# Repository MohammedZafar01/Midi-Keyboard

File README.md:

This innovative project is a compact, custom instrument driven by an ESP32-S3 microcontroller that features capacitive touch keys instead of traditional mechanical keyboard switches. It incorporates two potentiometers and one rotary encoder for real-time parameter tweaking, alongside three toggle switches to seamlessly shift octaves or change musical play modes. Visual feedback is provided dynamically through three integrated LEDs. Because the design utilizes every single available hardware pin on the microcontroller, it relies entirely on its existing micro-USB port to transmit data rather than requiring extra audio outputs. By leveraging native USB MIDI capabilities, the device communicates directly with a computer or mobile phone to send instant, lightweight musical commands that trigger high-quality audio synthesis inside software like GarageBand or Ableton.

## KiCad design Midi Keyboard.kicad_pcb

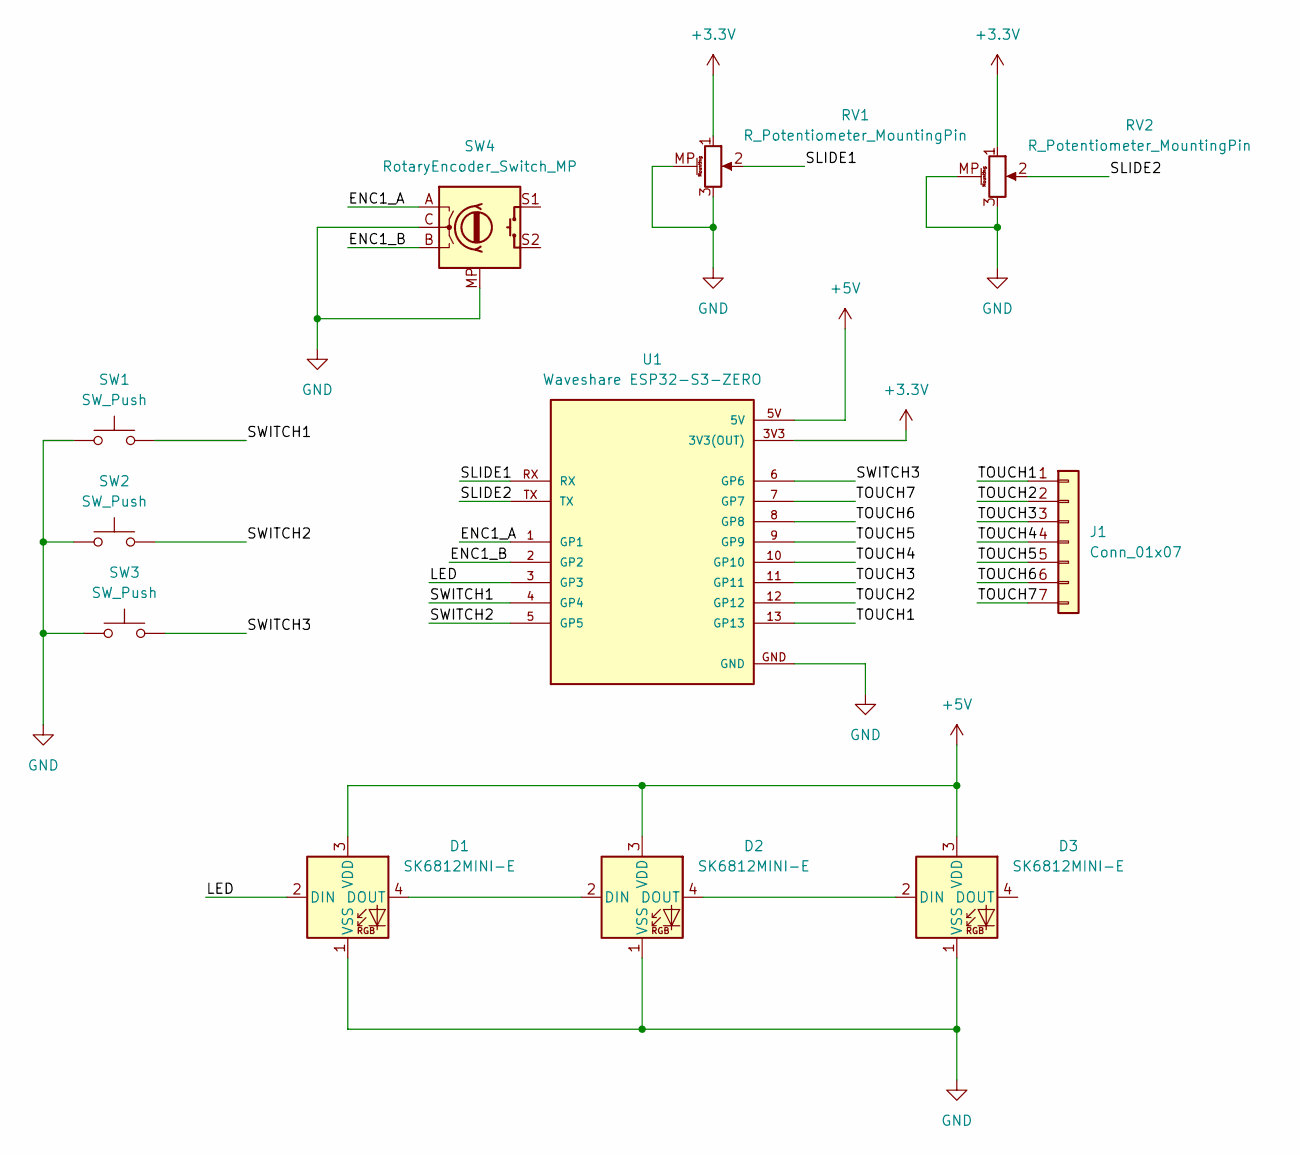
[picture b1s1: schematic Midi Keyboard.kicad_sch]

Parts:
D1, D2, D3: SK6812MINI-E; LED_SK6812MINI-E_3.2x2.8mm_P1.5mm_ReverseMount
J1: Conn_01x07; Untitled
RV1, RV2: R_Potentiometer_MountingPin; Potentiometer_Bourns_PTA1543_Single_Slide
SW1, SW2, SW3: SW_Push; Kailh Choc Low-Profile Switches
SW4: RotaryEncoder_Switch_MP; RotaryEncoder_Alps_EC11E-Switch_Vertical_H20mm
U1: Waveshare ESP32-S3-ZERO; Waveshare ESP32-S3-Zero; PARTREV NA

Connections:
+3.3V: RV1.1, RV2.1, U1.3V3 (3V3(OUT))
+5V: D1.3 (VDD), D2.3 (VDD), D3.3 (VDD), U1.5V
/ENC1_A: SW4.A, U1.1 (GP1)
/ENC1_B: SW4.B, U1.2 (GP2)
/LED: D1.2 (DIN), U1.3 (GP3)
/SLIDE1: RV1.2, U1.RX
/SLIDE2: RV2.2, U1.TX
/SWITCH1: SW1.2, U1.4 (GP4)
/SWITCH2: SW2.2, U1.5 (GP5)
/SWITCH3: SW3.2, U1.6 (GP6)
/TOUCH1: J1.1, U1.13 (GP13)
/TOUCH2: J1.2, U1.12 (GP12)
/TOUCH3: J1.3, U1.11 (GP11)
/TOUCH4: J1.4, U1.10 (GP10)
/TOUCH5: J1.5, U1.9 (GP9)
/TOUCH6: J1.6, U1.8 (GP8)
/TOUCH7: J1.7, U1.7 (GP7)
GND: D1.1 (VSS), D2.1 (VSS), D3.1 (VSS), RV1.3, RV1.MP (MountPin), RV2.3, RV2.MP (MountPin), SW1.1, SW2.1, SW3.1, SW4.C, SW4.MP, U1.GND
unnamed: D1.4 (DOUT), D2.2 (DIN)
unnamed: D2.4 (DOUT), D3.2 (DIN)

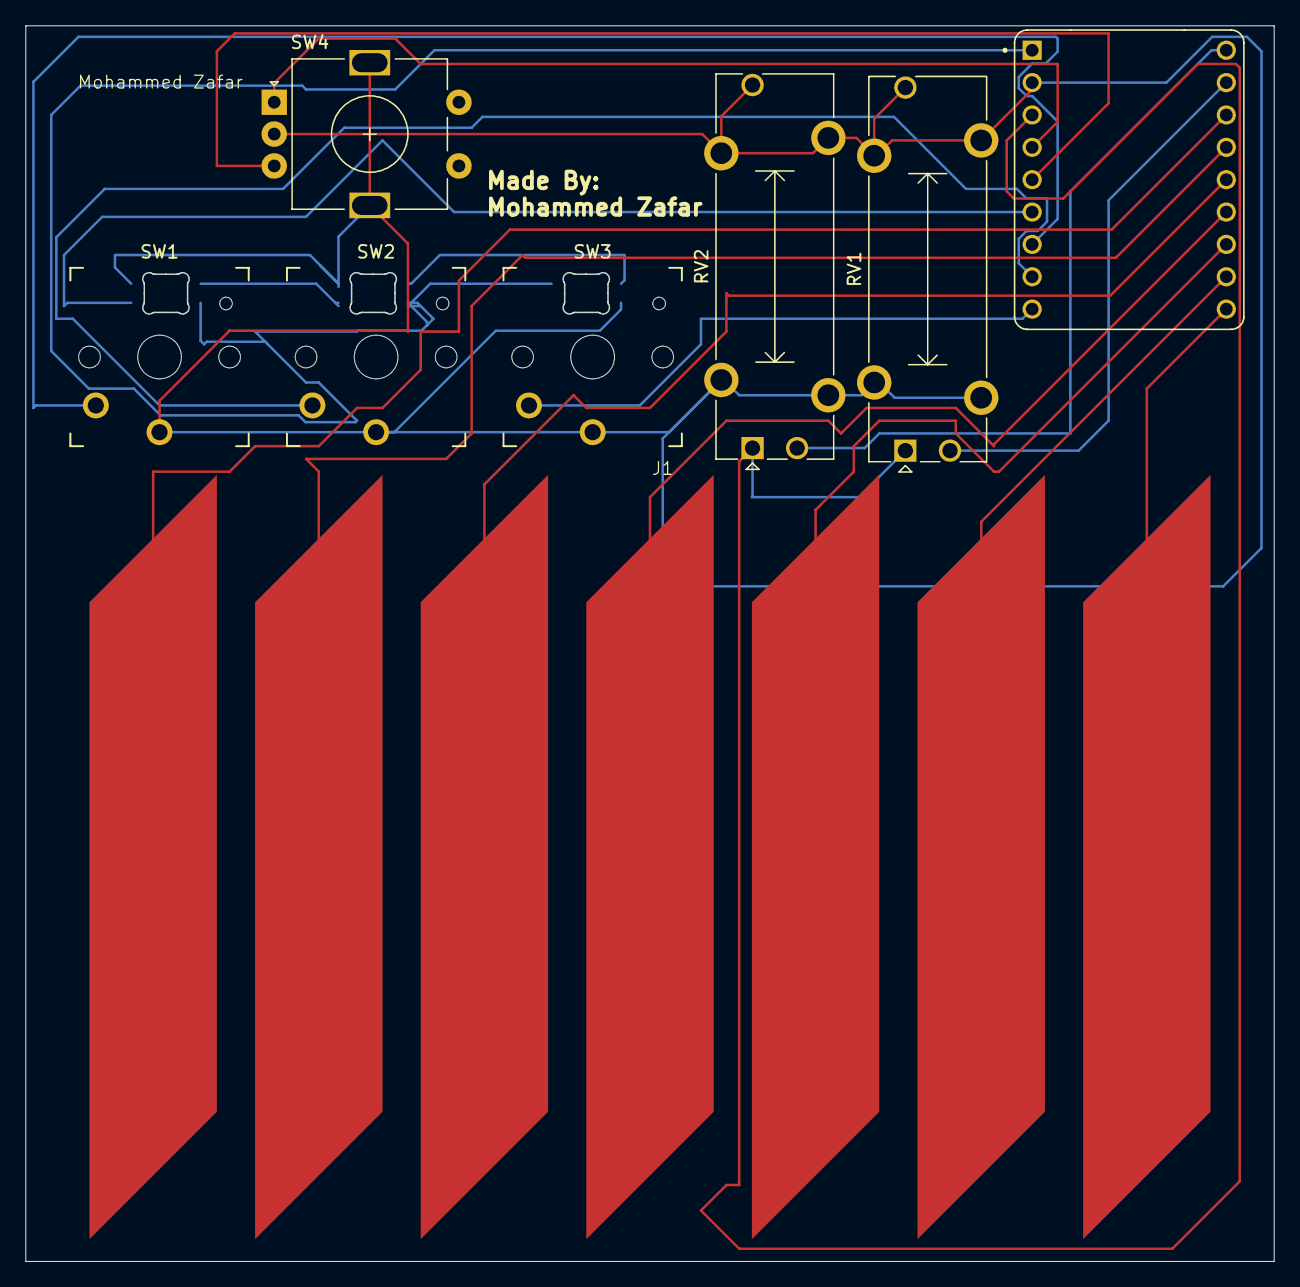
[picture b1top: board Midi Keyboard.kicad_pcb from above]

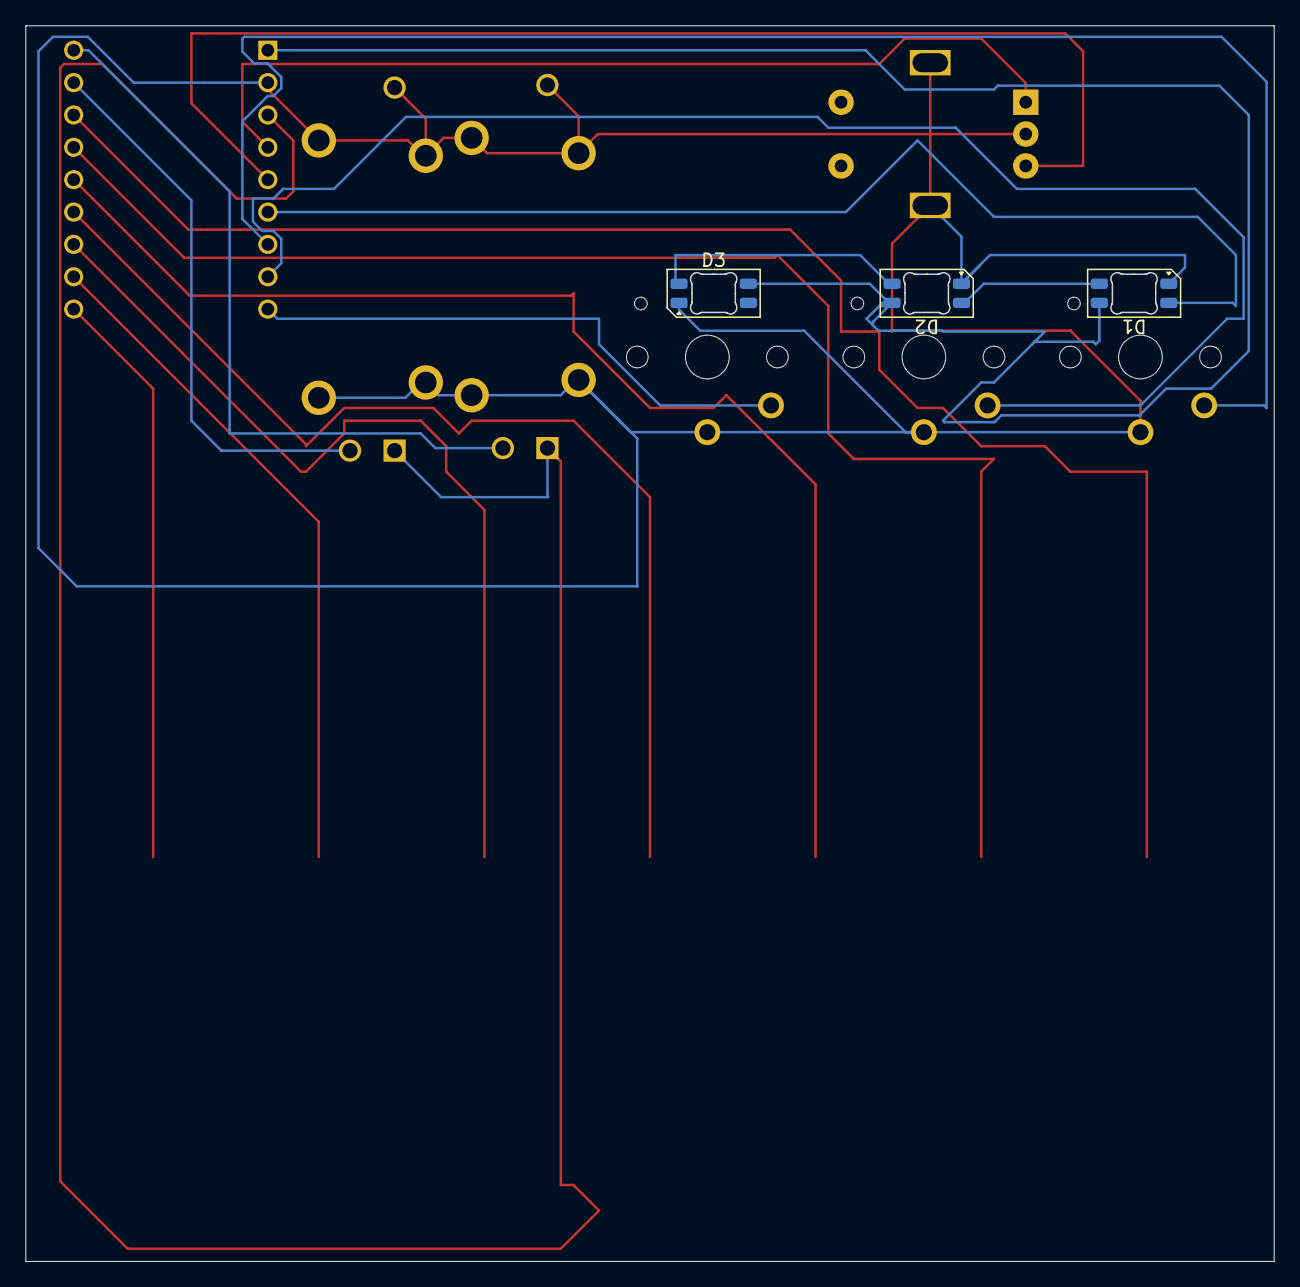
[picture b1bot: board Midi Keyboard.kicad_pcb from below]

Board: 2 copper layers, 98.0 x 97.0 mm, 11 parts (3 on the bottom side), 20 nets.
